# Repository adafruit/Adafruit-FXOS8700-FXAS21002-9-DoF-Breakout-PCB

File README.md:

## Adafruit FXOS8700 FXAS21002 9-DoF Breakout PCB

<a href="http://www.adafruit.com/products/3463"><br/>
Click here to purchase one from the Adafruit shop</a>

PCB files for the Adafruit FXOS8700 + FXAS21002 9 DoF Breakout. Format is EagleCAD schematic and board layout

For more details, check out the product page at
* https://www.adafruit.com/products/3463

### Description

The NXP Precision 9DoF breakout combines two of the best motion sensors we've tested here at Adafruit: The FXOS8700 3-Axis accelerometer and magnetometer, and the FXAS21002 3-axis gyroscope.

These two sensors combine to make a nice 9-DoF kit, that can be used for motion and orientation sensing. In particular, we think this sensor set is ideal for AHRS-based orientation calculations: the gyro stability performance is superior to the LSM9DS0, LSM9DS1, L3GD20H + LSM303, MPU-9250, and even the BNO-055 (see our Gyro comparison tutorial for more details).

Compared to the BNO055, this sensor will get you similar orientation performance but at a lower price because the calculations are done on your microcontroller, not in the sensor itself. The trade off is you will sacrifice about 15KB of Flash space, and computing cycles, to do the math 'in house.'

To make it fast and easy for you to get started, we have a version of AHRS that we've adapted to work over USB or Bluetooth LE. Load the code onto your Arduino-compatible board and you will get orientation data in the form of Euler angles or quaternions! It will work on a ATmega328 (the fusion code is 15KB of flash) but faster/larger chips such as M0 or ESP8266 will give you more breathing room.

Each board comes with the two chips soldered onto a breakout with 4 mounting holes. While the chips support SPI, they don't tri-state the MISO pin, so we decided to go with plain I2C which works well and is supported by every modern microcontroller and computer chip set.  There's a 3.3V regulator and level shifting on the I2C and Reset lines, so you can use the breakout safely with 3.3V or 5V power/logic. Each order comes with a fully assembled and tested breakout and a small strip of header. Some light soldering is required to attach the header if you want to use in a breadboard.

### License

Adafruit invests time and resources providing this open source design, please support Adafruit and open-source hardware by purchasing products from [Adafruit](https://www.adafruit.com)!

Designed by Limor Fried/Ladyada for Adafruit Industries.

Creative Commons Attribution/Share-Alike, all text above must be included in any redistribution. See license.txt for additional details.

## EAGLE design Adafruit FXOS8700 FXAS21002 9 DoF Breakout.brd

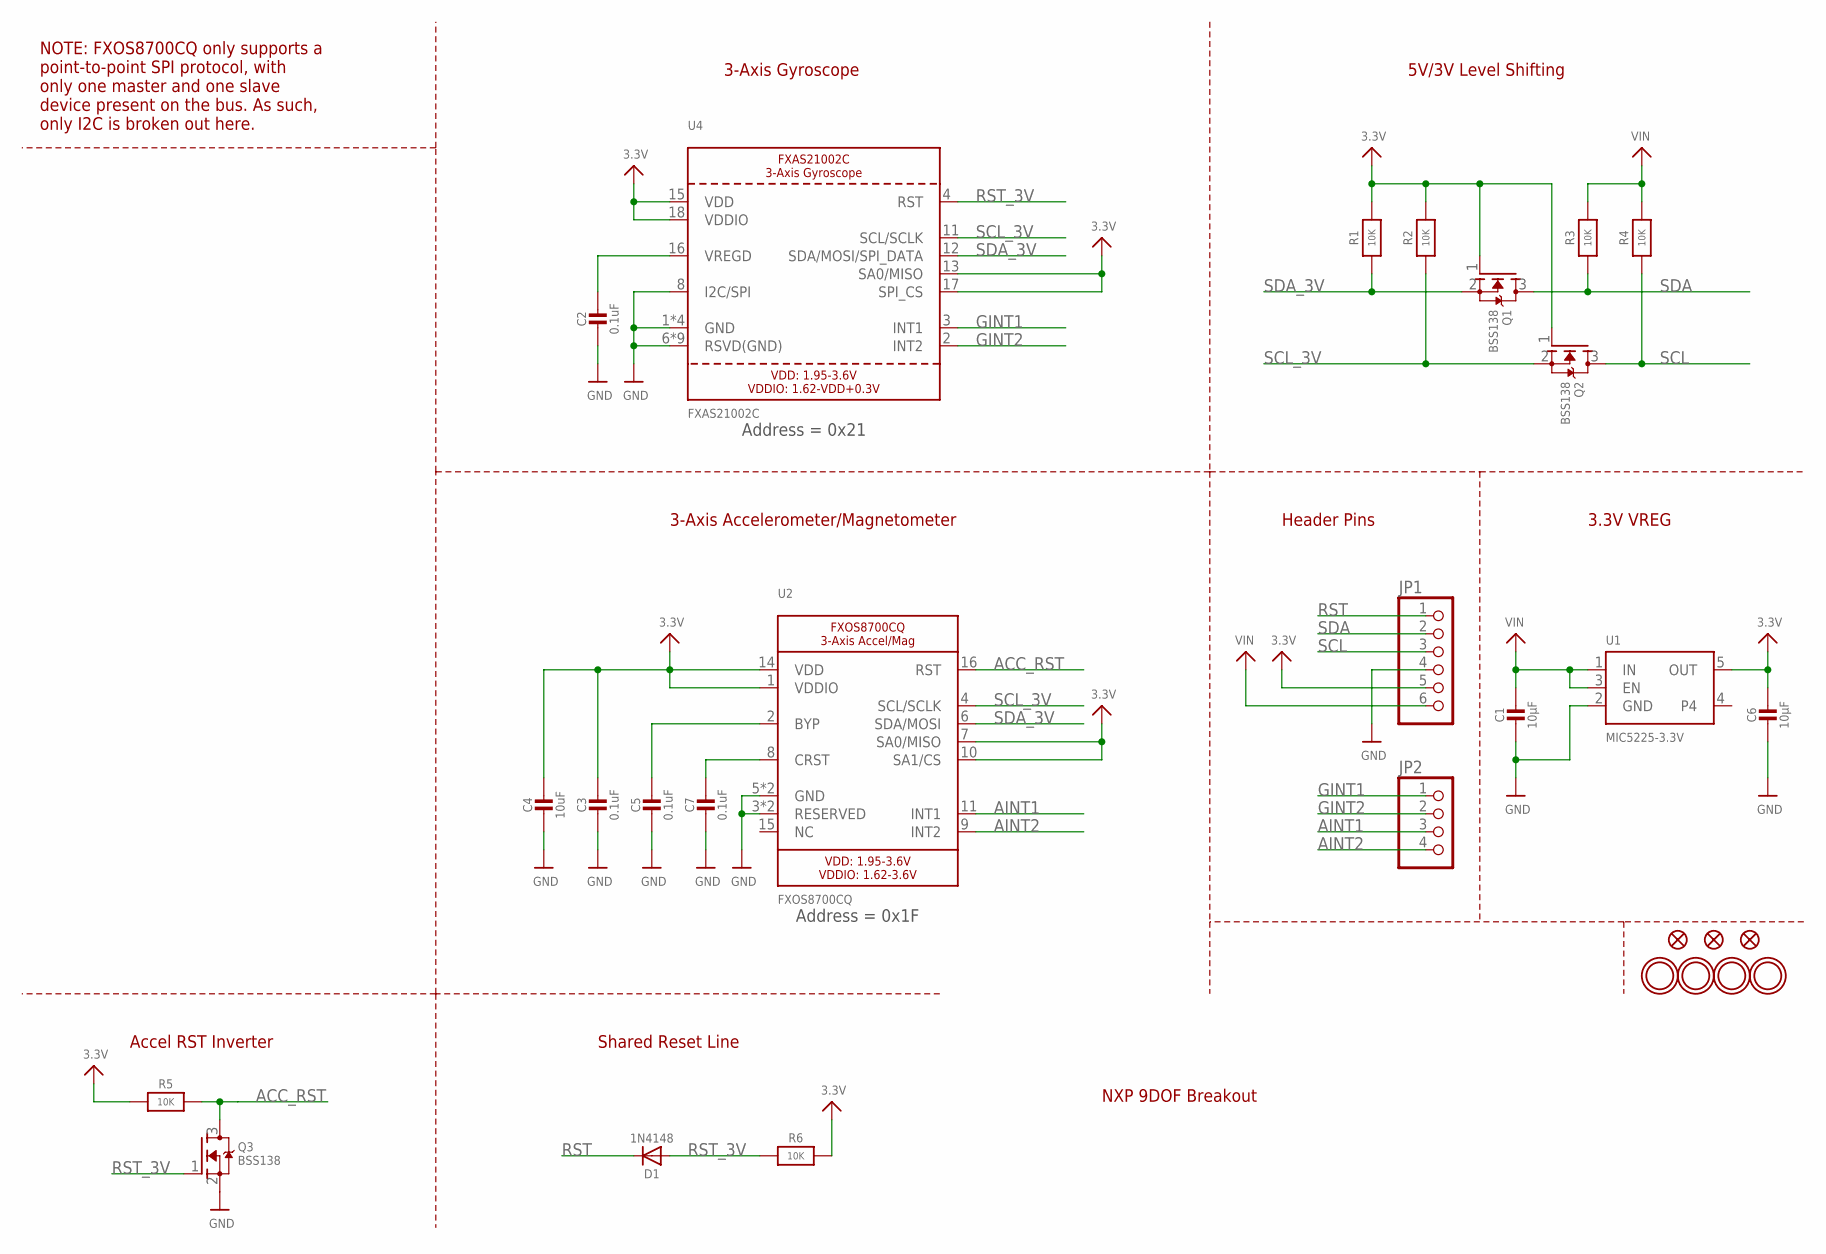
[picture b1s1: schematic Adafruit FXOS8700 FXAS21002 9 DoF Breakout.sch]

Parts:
C1, C6: 10µF; 0805-NO
C2, C3, C5, C7: 0.1uF; 0805-NO
C4: 10uF; 0805-NO
D1: 1N4148; SOD-323
FID1, FID2, FID3: FIDUCIAL_1MM
JP1: HEADER-1X670MIL; 1X06_ROUND_70
JP2: HEADER-1X4ROUND; 1X04_ROUND
Q1, Q2, Q3: BSS138; SOT23-WIDE
R1, R2, R3, R4, R5, R6: 10K; 0805-NO
U1: MIC5225-3.3V; SOT23-5
U2: FXOS8700CQ; QFN16_3MM_FREESCALE_5X3
U4: FXAS21002C; QFN24_4MM_FREESCALE_7X5
U$1, U$2, U$3, U$4: MOUNTINGHOLE2.5; MOUNTINGHOLE_2.5_PLATED

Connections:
3.3V: C3.1, C4.1, C6.1, JP1.5, Q1.1 (G), Q2.1 (G), R1.2, R2.2, R5.1, R6.2, U1.5 (OUT), U2.1 (VDDIO), U2.7 (SA0/MISO), U2.10 (SA1/CS), U2.14 (VDD), U4.13 (SA0/MISO), U4.15 (VDD), U4.17 (SPI_CS), U4.18 (VDDIO)
ACC_RST: Q3.3 (D), R5.2, U2.16 (RST)
AINT1: JP2.3, U2.11 (INT1)
AINT2: JP2.4, U2.9 (INT2)
GINT1: JP2.1, U4.3 (INT1)
GINT2: JP2.2, U4.2 (INT2)
GND: C1.2, C2.2, C3.2, C4.2, C5.2, C6.2, C7.2, JP1.4, Q3.2 (S), U1.2 (GND), U2.3 (RESERVED), U2.5 (GND), U2.12 (GND), U2.13 (RESERVED), U4.1 (GND), U4.5 (GND), U4.6 (RSVD(GND)), U4.7 (RSVD(GND)), U4.8 (I2C/SPI), U4.9 (RSVD(GND)), U4.10 (RSVD(GND)), U4.14 (GND), U4.19 (GND), U4.20 (RSVD(GND)), U4.21 (RSVD(GND)), U4.22 (RSVD(GND)), U4.23 (RSVD(GND)), U4.24 (RSVD(GND))
unnamed: C2.1, U4.16 (VREGD)
unnamed: C5.1, U2.2 (BYP)
unnamed: C7.1, U2.8 (CRST)
RST: D1.C, JP1.1
RST_3V: D1.A, Q3.1 (G), R6.1, U4.4 (RST)
SCL: JP1.3, Q2.3 (D), R4.1
SCL_3V: Q2.2 (S), R2.1, U2.4 (SCL/SCLK), U4.11 (SCL/SCLK)
SDA: JP1.2, Q1.3 (D), R3.1
SDA_3V: Q1.2 (S), R1.1, U2.6 (SDA/MOSI), U4.12 (SDA/MOSI/SPI_DATA)
VIN: C1.1, JP1.6, R3.2, R4.2, U1.1 (IN), U1.3 (EN)

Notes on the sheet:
Address = 0x21
Address = 0x1F
3-Axis Accelerometer/Magnetometer
3-Axis Gyroscope
5V/3V Level Shifting
3.3V VREG
Shared Reset Line
NXP 9DOF Breakout
Header Pins
NOTE: FXOS8700CQ only supports a point-to-point SPI protocol, with only one master and one slave device present on the bus. As such, only I2C is broken out here.
Accel RST Inverter

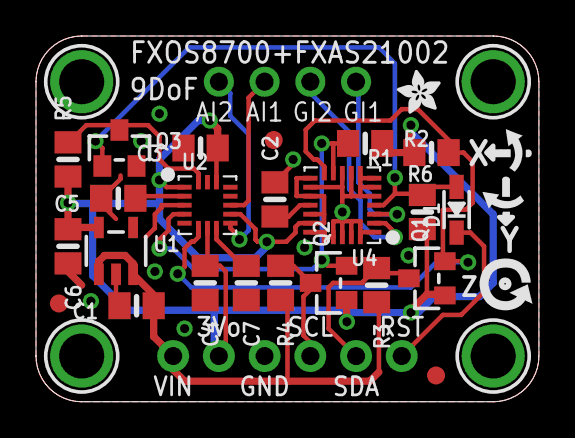
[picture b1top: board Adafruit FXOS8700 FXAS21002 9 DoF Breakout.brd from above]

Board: 2 copper layers, 27.9 x 20.3 mm, 34 parts (1 on the bottom side), 17 nets.

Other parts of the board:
U$26: ADAFRUIT_2.5MM
U$27: SYMBOL_GYRO_CCLOCKWISE
U$28: SYMBOL_GYRO_CLOCKWISE
U$31: SYMBOL_GYRO_Z
U$32: PCBFEAT-REV-040

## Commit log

2017-04-11 init!

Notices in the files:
parts and their libraries:
microbuilder: This work is placed in the public domain, and may be freely used for commercial and non-commercial work with the following conditions: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
